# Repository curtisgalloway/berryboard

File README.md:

# Berryboard

A Raspberry Pi HAT+ for ROV (remotely operated vehicle) control, with an RP2350B co-processor for hard real-time servo and sensor management.

## Overview

Berryboard sits on top of a Raspberry Pi 4 or 5 and handles the latency-sensitive workload that the Linux kernel can't guarantee: PWM servo output, sensor polling, and leak detection. The RPi handles high-level control logic over UART; the RP2350B handles everything that needs deterministic timing.

```
┌─────────────────────────────────────────────┐
│                  Raspberry Pi               │
│                  (host computer)            │
└──────────────┬──────────────────────────────┘
               │ 40-pin HAT header
┌──────────────▼──────────────────────────────┐
│                  Berryboard                  │
│                                             │
│  RP2350B ────── 8× servo outputs (PWM)      │
│           ────── IMU (ICM-42688-P, SPI)     │
│           ────── Magnetometer (MMC5983MA)   │
│           ────── 2× leak sensors (ADC)      │
│           ────── Servo power monitor (ADC)  │
│                                             │
│  TPS2121 power mux                          │
│    IN1: XT30 external servo power           │
│    IN2: RPi 5V from header                  │
│    OUT: 5V system rail                      │
│                                             │
│  6× QWIIC connectors                        │
│    3× on RPi I2C1 (GPIO2/3 on header)       │
│    3× on RP2350B I2C                        │
└─────────────────────────────────────────────┘
```

## Hardware Features

| Feature | Detail |
|---------|--------|
| Form factor | 65 × 56 mm RPi HAT+ |
| Co-processor | RP2350B (dual Arm Cortex-M33 / RISC-V, 520 KB SRAM) |
| Flash | W25Q16JVSS 2 MB QSPI (RP2350B) |
| EEPROM | 24LC32 (HAT ID, I2C0) |
| Servo outputs | 8 channels — 3× 1×8 Dupont block (signal / power / GND) |
| Servo power | XT30 connector, monitored via ADC |
| IMU | ICM-42688-P 6-axis (accel + gyro), SPI to RPi |
| Magnetometer | MMC5983MA 3-axis, I2C to RPi |
| QWIIC | 6× JST-SH 1 mm (3 RPi + 3 MCU) |
| Leak detection | 2× probes → RP2350B ADC |
| Status LED | WS2812B RGB (RP2350B GPIO12) |
| USB-C | USB 2.0 to RP2350B (programming / debug edge connector) |
| SWD | 4-pin header (J21) |
| Host link | UART (GPIO14/15 on 40-pin header); optional USB-C |
| Power | 5V from XT30 or RPi header, muxed by TPS2121 |
| 3.3V | AP2112K LDO from 5V system rail |

## Servo Connector

The 8 servo channels use three color-coded 1×8 Dupont headers placed side-by-side:

```
Pin:     1    2    3    4    5    6    7    8
         ┌────┬────┬────┬────┬────┬────┬────┐
Yellow   │ S0 │ S1 │ S2 │ S3 │ S4 │ S5 │ S6 │ S7 │  Signal
         ├────┼────┼────┼────┼────┼────┼────┤────┤
Red      │+V  │+V  │+V  │+V  │+V  │+V  │+V  │+V  │  SERVO_PWR
         ├────┼────┼────┼────┼────┼────┼────┤────┤
Black    │GND │GND │GND │GND │GND │GND │GND │GND │  GND
         └────┴────┴────┴────┴────┴────┴────┘────┘
```

Pin 1 = servo channel 1 (SERVO_0 net). Plug a standard 3-pin servo Dupont connector into any column.

## Repository Contents

| File | Description |
|------|-------------|
| `berryboard.kicad_sch` | Schematic |
| `berryboard.kicad_pcb` | PCB layout |
| `berryboard-custom.kicad_sym` | Custom KiCad symbols (TPS2121, ICM-42688-P, MMC5983MA) |
| `sym-lib-table` | KiCad symbol library table |

## Status

- [x] Schematic complete (0 ERC errors)
- [x] Footprints assigned
- [ ] PCB layout and routing
- [ ] Design rule check
- [ ] BOM verification (JLCPCB availability)
- [ ] Bring-up and testing

## Tools

Designed with [KiCad](https://www.kicad.org/) 9.x.

## License

Hardware design files are released under [CERN Open Hardware Licence Version 2 – Permissive (CERN-OHL-P)](https://ohwr.org/cern_ohl_p_v2.txt).

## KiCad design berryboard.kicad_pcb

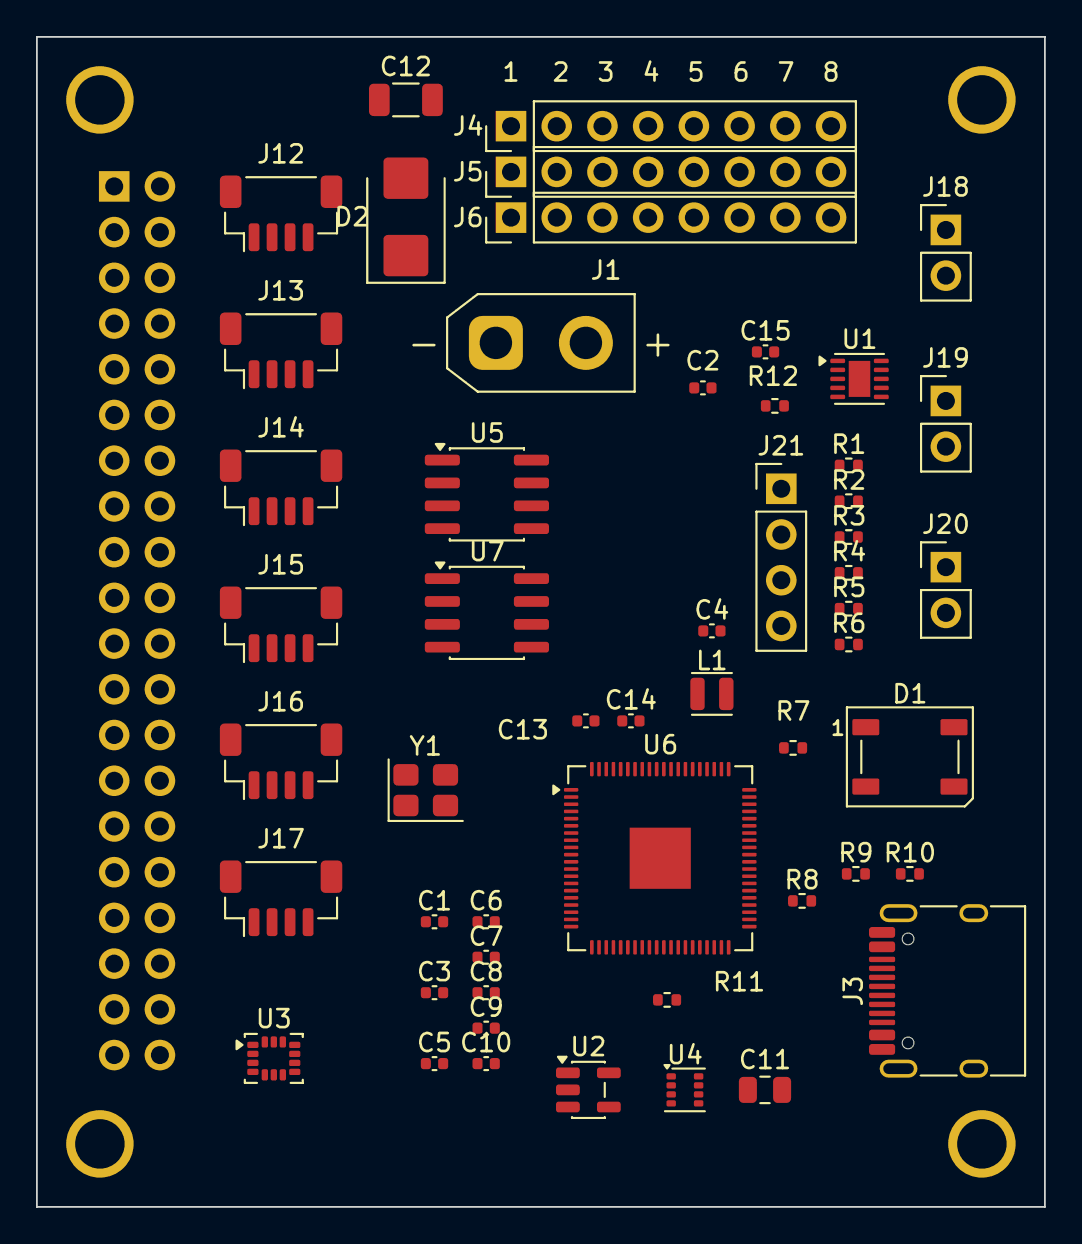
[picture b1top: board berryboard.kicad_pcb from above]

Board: 2 copper layers, 56.0 x 65.0 mm, 58 parts (1 on the bottom side), 53 nets, no tracks yet.

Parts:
C1, C5, C6, C7, C8, C9: 100nF; C_0402_1005Metric
C2, C4, C15: 4.7uF; C_0402_1005Metric
C3, C10: 10uF; C_0402_1005Metric
C11: 47uF; C_0805_2012Metric
C12: 100uF; C_1206_3216Metric
C13, C14: 15pF; C_0402_1005Metric
D1: WS2812B; LED_WS2812B_PLCC4_5.0x5.0mm_P3.2mm
D2: SMBJ7.5A; D_SMB
J1: XT30_SERVO_PWR; AMASS_XT30UPB-F_1x02_P5.0mm_Vertical
J2: RPi_GPIO_40P; PinSocket_2x20_P2.54mm_Vertical
J3: USB_C_RP2350; USB_C_Receptacle_HRO_TYPE-C-31-M-12
J4: SERVO_SIG; PinHeader_1x08_P2.54mm_Vertical
J5: SERVO_PWR; PinHeader_1x08_P2.54mm_Vertical
J6: SERVO_GND; PinHeader_1x08_P2.54mm_Vertical
J12: QWIIC_RPI_1; JST_SH_BM04B-SRSS-TB_1x04-1MP_P1.00mm_Vertical
J13: QWIIC_RPI_2; JST_SH_BM04B-SRSS-TB_1x04-1MP_P1.00mm_Vertical
J14: QWIIC_RPI_3; JST_SH_BM04B-SRSS-TB_1x04-1MP_P1.00mm_Vertical
J15: QWIIC_MCU_1; JST_SH_BM04B-SRSS-TB_1x04-1MP_P1.00mm_Vertical
J16: QWIIC_MCU_2; JST_SH_BM04B-SRSS-TB_1x04-1MP_P1.00mm_Vertical
J17: QWIIC_MCU_3; JST_SH_BM04B-SRSS-TB_1x04-1MP_P1.00mm_Vertical
J18: LEAK_1; PinHeader_1x02_P2.54mm_Vertical
J19: LEAK_2; PinHeader_1x02_P2.54mm_Vertical
J20: HAT_5V_IN; PinHeader_1x02_P2.54mm_Vertical
J21: SWD; PinHeader_1x04_P2.54mm_Vertical
L1: AOTA-B201610S3R3-101-T; L_Wuerth_PMCI-201610
MH1, MH2, MH3, MH4: MountingHole_2.75mm
R1, R2: 5.1k; R_0402_1005Metric
R3, R4, R5, R6: 4.7k; R_0402_1005Metric
R7: 220k; R_0402_1005Metric
R8: 100k; R_0402_1005Metric
R9, R10: 27; R_0402_1005Metric
R11: 1k; R_0402_1005Metric
R12: 33; R_0402_1005Metric
U1: TPS2121; WSON-10-1EP_2.5x2.5mm_P0.5mm_EP1.2x2mm
U2: AP2112K-3.3; SOT-23-5
U3: ICM-42688-P; LGA-14_3x2.5mm_P0.5mm_LayoutBorder3x4y
U4: MMC5983MA; Broadcom_LGA-8_2x2mm_P0.5mm
U5: 24LC32; SOIC-8_3.9x4.9mm_P1.27mm
U6: RP2350B; QFN-80-1EP_10x10mm_P0.4mm_EP3.4x3.4mm
U7: W25Q16JVSS; SOIC-8_3.9x4.9mm_P1.27mm
Y1: ABM8-272-T3; Crystal_SMD_3225-4Pin_3.2x2.5mm

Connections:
/+3.3V_RPI: J2.1, J2.17
/+3V3: C2.1, C3.1, C5.1, C6.1, C7.1, C8.1, J12.2, J13.2, J14.2, J15.2, J16.2, J17.2, J21.1, R3.1, R4.1, R5.1, R6.1, R12.1, U2.5, U3.5, U3.6, U4.4, U5.8, U6.5, U6.15, U6.24, U6.29, U6.35, U6.41, U6.50, U6.59, U6.60, U6.64, U6.68, U6.69, U6.76, U7.8
/+5V: C9.1, C10.1, D1.1, J3.A4, J3.A9, J3.B4, J3.B9, U1.6, U2.1, U2.3
/+5V_EXT: J20.1, U1.2, U1.3
/+5V_RPI: J2.2, J2.4, U1.1, U1.4
/FLASH_CLK: U6.71, U7.6
/FLASH_CS: U6.75, U7.1
/FLASH_IO0: U6.72, U7.5
/FLASH_IO1: U6.74, U7.2
/FLASH_IO2: U6.73, U7.3
/FLASH_IO3: U6.70, U7.7
/I2C0_SCL: J2.28, U5.6
/I2C0_SDA: J2.27, U5.5
/I2C1_SCL: J2.5, J12.4, J13.4, J14.4, R6.2, U4.5
/I2C1_SDA: J2.3, J12.3, J13.3, J14.3, R5.2, U4.6
/IMU_INT1: J2.36, U3.3
/LEAK_ADC0: J18.1, U6.52
/LEAK_ADC1: J19.1, U6.53
/MCU_AVDD: C15.1, R12.2, U6.61
/MCU_DVDD: C1.1, C4.1, L1.2, U6.10, U6.32, U6.51, U6.65
/MCU_LX: L1.1, U6.63
/MCU_SCL: J15.4, J16.4, J17.4, R4.2, U6.9
/MCU_SDA: J15.3, J16.3, J17.3, R3.2, U6.8
/MMC_C1: C11.1, U4.8
/MMC_C2: C11.2, U4.3
/NEOPIXEL: D1.4, U6.11
/SERVO_0: J4.7, U6.77
/SERVO_1: J4.6, U6.78
/SERVO_2: J4.5, U6.79
/SERVO_3: J4.4, U6.80
/SERVO_4: J4.3, U6.1
/SERVO_5: J4.2, U6.2
/SERVO_6: J4.1, U6.3
/SERVO_MON: R7.2, R8.1, U6.54
/SERVO_PWR: C12.1, D2.2, J1.1, J5.1, J5.2, J5.3, J5.4, J5.5, J5.6, J5.7, R7.1
/SPI0_CE0: J2.24, U3.12
/SPI0_MISO: J2.21, U3.9
/SPI0_MOSI: J2.19, U3.10
/SPI0_SCLK: J2.23, U3.11
/SWCLK: J21.4, U6.33
/SWDIO: J21.2, U6.34
/UART_RX: J2.10, U6.6
/UART_TX: J2.8, U6.7
/USB_CC1: J3.A5, R1.1
/USB_CC2: J3.B5, R2.1
/USB_DM: J3.A7, J3.B7, R10.1
/USB_DM_MCU: R10.2, U6.66
/USB_DP: J3.A6, J3.B6, R9.1
/USB_DP_MCU: R9.2, U6.67
/XIN: C13.1, U6.30, Y1.1
/XOUT: C14.1, R11.1, Y1.2
/XOUT_MCU: R11.2, U6.31
GND: C1.2, C2.2, C3.2, C4.2, C5.2, C6.2, C7.2, C8.2, C9.2, C10.2, C12.2, C13.2, C14.2, C15.2, D1.3, D2.1, J1.2, J2.6, J2.9, J2.14, J2.20, J2.25, J2.30, J2.34, J2.39, J3.A1, J3.A8, J3.A12, J3.B1, J3.B8, J3.B12, J3.SH, J6.1, J6.2, J6.3, J6.4, J6.5, J6.6, J6.7, J12.1, J13.1, J14.1, J15.1, J16.1, J17.1, J18.2, J19.2, J20.2, J21.3, R1.2, R2.2, R8.2, U1.5, U1.7, U1.9, U2.2, U3.4, U3.7, U3.8, U3.13, U4.1, U4.2, U5.1, U5.2, U5.3, U5.4, U5.7, U6.62, U6.81, U7.4
